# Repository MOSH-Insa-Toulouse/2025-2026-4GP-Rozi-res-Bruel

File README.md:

# 2025-2026-4CP - Projet de capteur low-tech en graphite - Marilou Rozières & Adélaïs Bruel 

## SOMMAIRE
*** 
  - [I. Contexte et description du projet](#contexte-et-description-du)
  - [II. Livrables](#livrables)
  - [III. Matériel nécessaire](#matériel-nécessaire)
  - [IV. Conditionnement analogique](#conditionnement-analogique)
  - [V. Modélisaiotn et simulation](#modélisaiton-et-simulation)
  - [VI. Conception](#conception)
  - [VII. Fabrication](#fabrication)
  - [VIII. Développement firmware et software](#développement-firmware-et-software)
  - [IX. Analyse et caractérisation](#analyse-et-caractérisation)
  - [X. Datasheet](#datasheet)
  - [XI. Conclusion](#conclusion)

*** 

## Contexte et description du projet 

&nbsp;&nbsp;&nbsp;&nbsp;&nbsp;&nbsp;Ce projet s'inscrit dans le cadre de l'UF "Du capteur au banc de test" de la 4ème année Génie Physique de l'INSA Toulouse. 
L'objectif de ce projet est de concevoir, modéliser, prototyper, caractériser et analyser un capteur de déformation low-tech.

&nbsp;&nbsp;&nbsp;&nbsp;&nbsp;&nbsp;Le principe de fonctionnement du capteur repose sur la piézorésistivité d'un dépôt de graphite (réalisé à l'aide d'un simple crayon de bois) sur un support flexible (une feuille de papier). 
Microscopiquement, le trait de crayon est un agglomérat de feuillets de graphite. Dans ce milieu granulaire complexe, la conduction se fait principalement par effet tunnel : les nombreux grains sont séparés par de très fins interstices, la probabilité de passage des électrons d'un grain de graphite à l'autre par franchissement de l'interstice est non nulle si cette barrière est suffisament fine. Cette probabilité dépend exponentiellement de la distance *d* qui sépare les deux grains.
Ce paramètre physique est alors à l'origine de la variation de résistance : en tension, l'écart *d* entre les particules augmente, la probabilité de passage est plus faible, la résistance globale du capteur augmente. 
Tandis qu'en compression, la distance *d* diminue, les particules se rapprochent, la probabilité d'échange augmente, la résistance chute. 
La dépendance exponentielle de la résistance à la distance *d* explique pourquoi une très faible variation du capteur va nous permettre de lire des varirations de signal (résistance) importantes. 

&nbsp;&nbsp;&nbsp;&nbsp;&nbsp;Pour passer d'un trait de crayon à un capteur fonctionnel, le projet s'est déroulé selon ces différentes phases :
- **Conditionnement analogique** : Conception d'un amplificateur transimpédance (conversion courant-tension) pour transformer les variations de courant (de l'ordre du nA) en un signal de tension exploitable (0−5V).
- **Modélisation et Simulation** : Utilisation de LTSpice pour dimensionner les filtres actifs et passifs afin d'éliminer le bruit parasite (notamment le 50 Hz du secteur).
- **Conception** : Routage d'un circuit imprimé (Shield PCB) sous KiCad pour intégrer l'électronique, l'écran OLED et le module Bluetooth.
- **Fabrication** : Réalisation physique du PCB par insolation, gravure chimique (perchlorure de fer), perçage et soudure des composants.
- **Développement Firmware & Software** : Programmation de la carte Arduino (gestion de l'I2C, SPI et UART) et création d'une interface mobile sous MIT App Inventor.
- **Analyse** : Caractérisation du capteur sur un banc de test dédié et rédaction d'une datasheet technique.

Ce document a pour objectif d'expliciter ces différentes étapes.  

## Livrables 
Les livrables attendus sont les suivants : 
- **Un shield PCB connecté à une carte arduino UNO** avec différents composants : un capteur graphite, un amplificateur transimpédance, un module bluetooth, un écran OLED, un flex sensor commercial, un potentiomètre digital, un encodeur rotatoire. D'autres composants peuvent être implémentés ;
- **Un code arduino** qui gère les différents composants cités précédemments (mesures de contraintes, échanges bluetooth et OLED, potentiomètre digital et boutons) ;
- **Une application Android** (sous MIT App Inventor) interfaçant le PCB et le code Arduino correspondant;
- **Une datasheet du capteur** reprenant toutes ses caractéristiques ainsi que ses tests.

## Matériel nécessaire

Afin de réaliser notre dispositif électronique, nous avons eu besoin de :

**Pour le montage amplificateur transimpédance :**

- Résistances : une de 1 kΩ, une de 10 kΩ et deux de 100 kΩ - une troisième de 100 kΩ peut être prévue, mais peut aussi être substituée par une résistance variable (le potentiomètre digital), choix que l'on a fait ;
- Potentiomètre digital MCP41050 et son support ;
- Amplificateur opérationnel LTC1050 et son support ;
- Capacités : trois de 100 nF et une de 1 μF.

**Pour le reste du dispositif :**

- Arduino Uno et son câble d’alimentation ;
- Résistance : une de 47kΩ pour le flex sensor ;
- Module Bluetooth HC05 ;
- Ecran OLED de dimension 128*64 ;
- Flex sensor ;
- Encodeur rotatoire ;
- Capteur graphite et 2 pinces crocodiles ;
- 20 sockets ;
- 35 headers.

## Conditionnement analogique 

&nbsp;&nbsp;&nbsp;&nbsp;&nbsp;Le capteur en graphite présente une résistance extrêmement élevée (de l'ordre du MΩ), ce qui génère des courants infimes (pico- à nanoampères) sous une tension de 5 V. Pour transformer ce signal en une tension exploitable par l’ADC d'une Arduino UNO (0−5V), nous avons conçu un amplificateur transimpédance, réalisé comme suit : 

Nous avons utilisé l’AOP LTC1050 car il possède un courant de biais d'entrée extrêmement faible et un offset quasi nul, évitant ainsi de fausser les mesures de courants très faibles. 
Nous avons placé une résistance de protection (R5) en entrée pour protéger l'AOP contre les décharges électrostatiques, ainsi qu'une résistance du shunt (R1) qui assure la référence à la masse. La résistance de rétroaction (R2) a été subsitué par un potentiomètre digital MCP41050 pour ajuster dynamiquement le gain du montage via le code Arduino. 
Les trois étages de filtrages de cet amplificateur permet de minimiser au maximum les bruits parasites. 

## Modélisation et simulation 

&nbsp;&nbsp;&nbsp;&nbsp;&nbsp;Avant la fabrication, l'ensemble du circuit a été modélisé sous LTSpice pour vérifier que l'amplification convertit bien les nanoampères en une tension comprise entre 0 et 5V. Cette modélisation a également permis de valider l'efficacité de nos trois étage de filtrage :  
- Filtre passe-bas (16 Hz) : élimination des hautes fréquences parasites.
- Filtre passe-bas (1,6 Hz) : atténuation drastique du bruit secteur (50 Hz)
- Filtre passe-bas (1,6 kHz) : supression des interférences liées à la communication de l'ADC.

## Conception 
&nbsp;&nbsp;&nbsp;&nbsp;&nbsp;La phase de conception a été réalisée sur Kicad. L'ojectif était de créer un Shield compatible avec le format de l'Arduino UNO. 
Cela nous demandé trois étapes : 
- Saisie des empreintes et des shématics associés pour nos différents composants : AOP, potentiomètre digital, écran OLED, encodeur rotatoire et module bluetooth. 
- Le routage du PCB : optimisation du placement des composants pour réduire les longueurs de pistes et visualisation 3D des composants pour vérifier l'abscence de conflits mécaniques entre tous les composants.
- Ajout d'un plan de masse pour minimiser le bruit électromagnétique et stabiliser les mesures de hautes impédances.

## Fabrication 
&nbsp;&nbsp;&nbsp;&nbsp;&nbsp;La réalisation du prototype a été faite par ce processus de fabrication : 
- Insolation & gravure (réalisé par Catherine Crouzet) : transfert du masque de gravure sur une plaque époxy et passage au perchlorure de fer.
- Nettoyage (réalisé par Catherine Crouzet) : Retrait de la résine photosensible à l'acétone pour révéler les pistes de cuivre.
- Percage & soudure : montage manuel des composants sur le PCB final.
- Assemblage : soudure des composants.

## Développement Firmaware et Software 

Le système est piloté par deux pôles : 
- Firmware (Arduino) : utilisation des bibliothèques *Adafruit_SSD1306* (OLED), *SPI* (potentiomètre) et *SoftwareSerial* (Bluetooth). Le code génère un menu intéractif via l'encodeur rotatoire pour calibrer le capteur et lancer les mesures.
- Interface mobile : développement d'une application Android sur MIT App Inventor qui communique en Bluetooth pour afficher la résistance en temps réel et tracer la courbe de déformation directement sur le smartphone.

## Analyse et caractérisation

**Dispositif de mesure :** 

&nbsp;&nbsp;&nbsp;&nbsp;&nbsp;Afin d’obtenir les caractéristiques spécifiques du capteur, nous avons utilisé un banc de test composé de six cylindres de diamètre différent, permettant d’étudier la résistance de notre capteur en tension et en compression pour six valeurs de contraintes connues.  

&nbsp;&nbsp;&nbsp;&nbsp;&nbsp;Nous avons choisi d’étudier trois types de crayons à papier différent : le B, le 3B et le 6B. Nous avons donc conçu trois capteurs différents, et avons déterminé pour chacun d’entre eux douze valeurs : six en compression et six en tension. Ces mesures nous ont permises d’établir la variation relative de résistance en fonction de la déformation grâce aux formules suivantes : 

Calcul de la déformation ∶ ε=  e/D

Avec e l’épaisseur du papier utilisé pour le capteur et D le diamètre du cylindre sur lequel est effectué la mesure. 

Calcul de la variation relative de résistance∶ ∆R/R0 (%)=  (R_mesuré-R0)/R0

**Résultats des mesures :**

En tension, nous obtenons alors la variation relative de résistance en fonction de la déformation suivante : 

En compression, nous obtenons la variation relative de la résistance en fonction de la déformation suivante : 

&nbsp;&nbsp;&nbsp;&nbsp;&nbsp;Les allures des courbes sont pertinentes : les crayons à papier sont constitués de graphite et d’un liant isolant (argile). Afin de comprendre la différence entre les différents types de crayons (B, 3B, 6B, …) il faut se pencher sur le seuil de percolation de ceux-ci. Le seuil de percolation représente la fraction volumique nécessaire de charge conductrice (ici le graphite) afin que celles-ci forment un réseau continu interconnecté à travers la matrice isolante (l’argile). A partir de ce seuil de matière conductrice, les propriétés macroscopiques du matériau basculent d’un comportement isolant à un comportement conducteur. Un crayon 6B est saturé en graphite et contient très peu d’argile (seuil de percolation largement dépassé), il représente alors un milieu très conducteur. Quand une déformation est appliquée au capteur, des micro fissures sont créées, mais il existe une multitude de chemins secondaires conducteurs, la résistance globale du capteur n’est que très peu impactée. A contrario, le crayon B a une mine dure, il contient une forte proportion d’argile (très proche du seuil de percolation), les grains de graphite sont plus dispersés dans la matrice d’argile isolante, lorsqu’une déformation est appliquée, les rares chemins électriques entre les grains de graphite se brise très facilement, la résistance varie alors fortement. 

**Analyse :**

&nbsp;&nbsp;&nbsp;&nbsp;&nbsp;La sensibilité (facteur de jauge k) est définie par : k=  (∆R/R0)/ε
Le crayon B possède la meilleure sensibilité puisque pour une déformation donnée il génère une plus grande variation de résistance. Diminuer la concentration de charge conductrice (en passant de 6B à B) augmente alors fortement la piézorésistivité du matériau. 
Pour conclure, pour une application requérant une grande sensibilité un capteur réalisé avec un crayon de type B est le mieux, néanmoins celui-ci aura tendance à « s’user » plus vite puisque que sa composition est au niveau du seuil de percolation. Tandis que pour une application nécessitant moins de précision mais plus de robustesse, un crayon très gras tel que le 6B conviendra mieux, puisque qu’étant très loin du seuil de percolation il peut être déformé plus de fois avant de ne plus avoir chemins conducteurs possible entre les particules.  

## Datasheet
La datasheet du capteur est disponible [ici](https://github.com/MOSH-Insa-Toulouse/2025-2026-4GP-Rozi-res-Bruel/blob/main/DATASHEET/DATASHEET.pdf)

## Conclusion 
&nbsp;&nbsp;&nbsp;&nbsp;&nbsp;Pour conclure ce projet, ce capteur low tech est adapté non pas à la lecture d’une valeur de résistance et donc de déformation mais plutôt à la détection d’un mouvement. Il serait également intéressant dans une application jetable puisque qu’au bout de 5/10 utilisations il n’est plus fonctionnel.

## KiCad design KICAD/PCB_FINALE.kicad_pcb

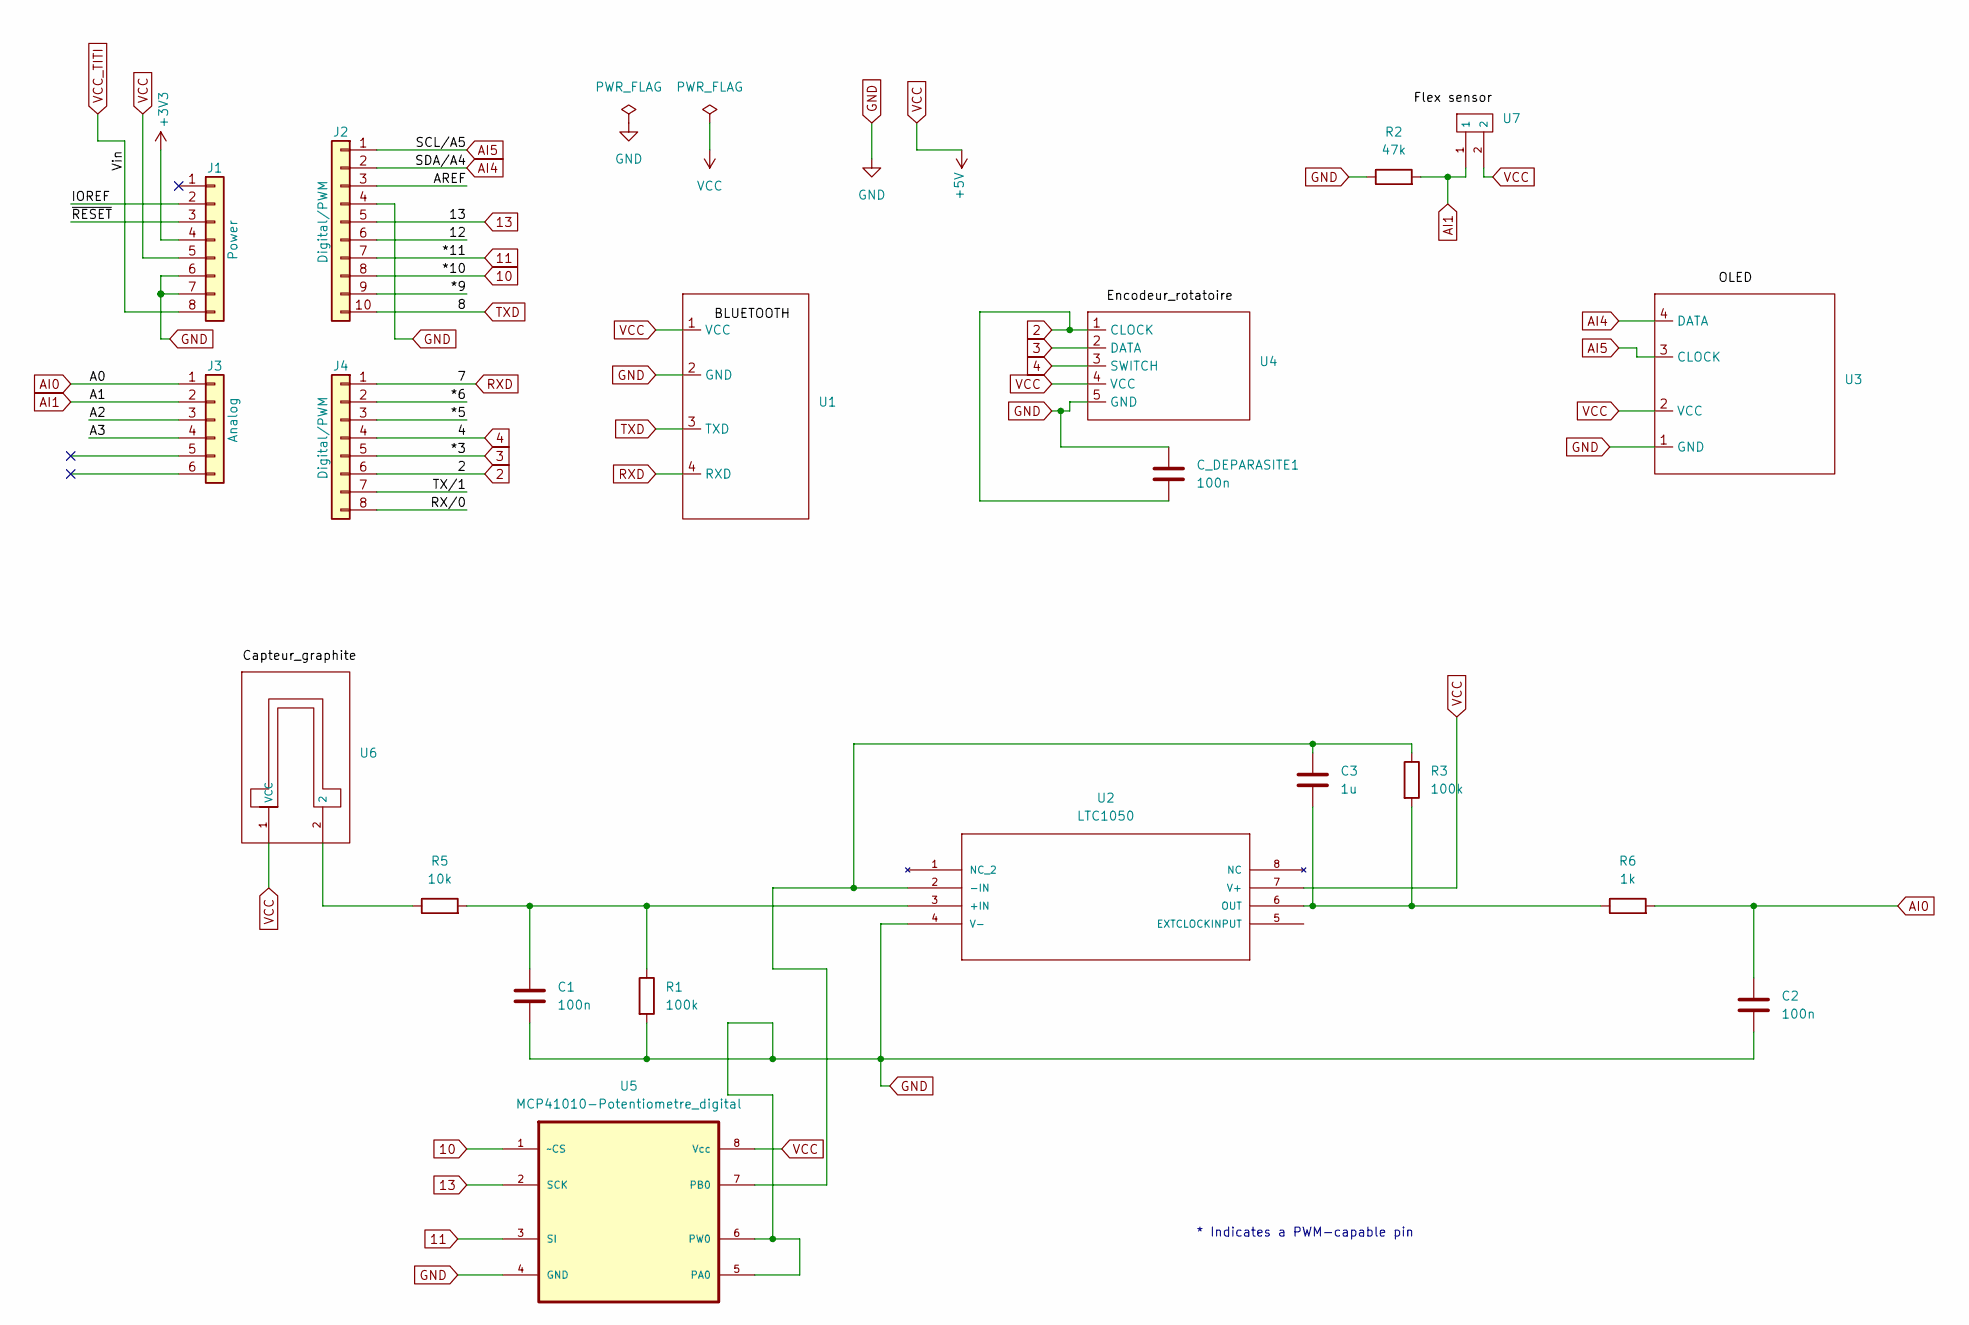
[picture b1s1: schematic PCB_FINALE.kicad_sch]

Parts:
C1, C2: 100n; CapaOk
C3: 1u; CapaOk
C_DEPARASITE1: 100n; CapaOk
J1: Power; PinSocket_1x08_P2.54mm_Vertical
J2: Digital/PWM; PinSocket_1x10_P2.54mm_Vertical
J3: Analog; PinSocket_1x06_P2.54mm_Vertical
J4: Digital/PWM; PinSocket_1x08_P2.54mm_Vertical
R1, R3: 100k; RES5
R2: 47k; RES5
R5: 10k; RES5
R6: 1k; RES5
U1: Bluetouth_HC05
U2: LTC1050; PDIP-8_N; MANUFACTURER_PART_NUMBER ltc1050cn8
U3: OLED_EMPREINTE
U4: ENCODEUR_ROTATOIRE
U5: MCP41010-Potentiometre_digital; Potentiomètre_digital
U6: capteur_graphite
U7: FLEX_SENSOR

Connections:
2: C_DEPARASITE1.2, J4.6, U4.1 (CLOCK)
3: J4.5, U4.2 (DATA)
4: J4.4, U4.3 (SWITCH)
10: J2.8, U5.1 (~CS)
11: J2.7, U5.3 (SI)
13: J2.5, U5.2 (SCK)
+3V3: J1.4
/12: J2.6
/*5: J4.3
/*6: J4.2
/*9: J2.9
/A2: J3.3
/A3: J3.4
/AREF: J2.3
/IOREF: J1.2
/RX/0: J4.8
/TX/1: J4.7
/~RESET: J1.3
AI0: C2.1, J3.1, R6.2
AI1: J3.2, R2.2, U7.1
AI4: J2.2, U3.4 (DATA)
AI5: J2.1, U3.3 (CLOCK)
GND: C1.2, C2.2, C_DEPARASITE1.1, J1.6, J1.7, J2.4, R1.2, R2.1, U1.2 (GND), U2.4 (V-), U3.1 (GND), U4.5 (GND), U5.4 (GND), U5.5 (PA0), U5.6 (PW0)
unnamed: R5.1, U6.2
unnamed: C1.1, R1.1, R5.2, U2.3 (+IN)
unnamed: C3.1, R3.1, U2.2 (-IN), U5.7 (PB0)
unnamed: C3.2, R3.2, R6.1, U2.6 (OUT)
RXD: J4.1, U1.4 (RXD)
TXD: J2.10, U1.3 (TXD)
VCC: J1.5, U1.1 (VCC), U2.7 (V+), U3.2 (VCC), U4.4 (VCC), U5.8 (Vcc), U6.1 (VCC), U7.2
VCC_TITI: J1.8

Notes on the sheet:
* Indicates a PWM-capable pin

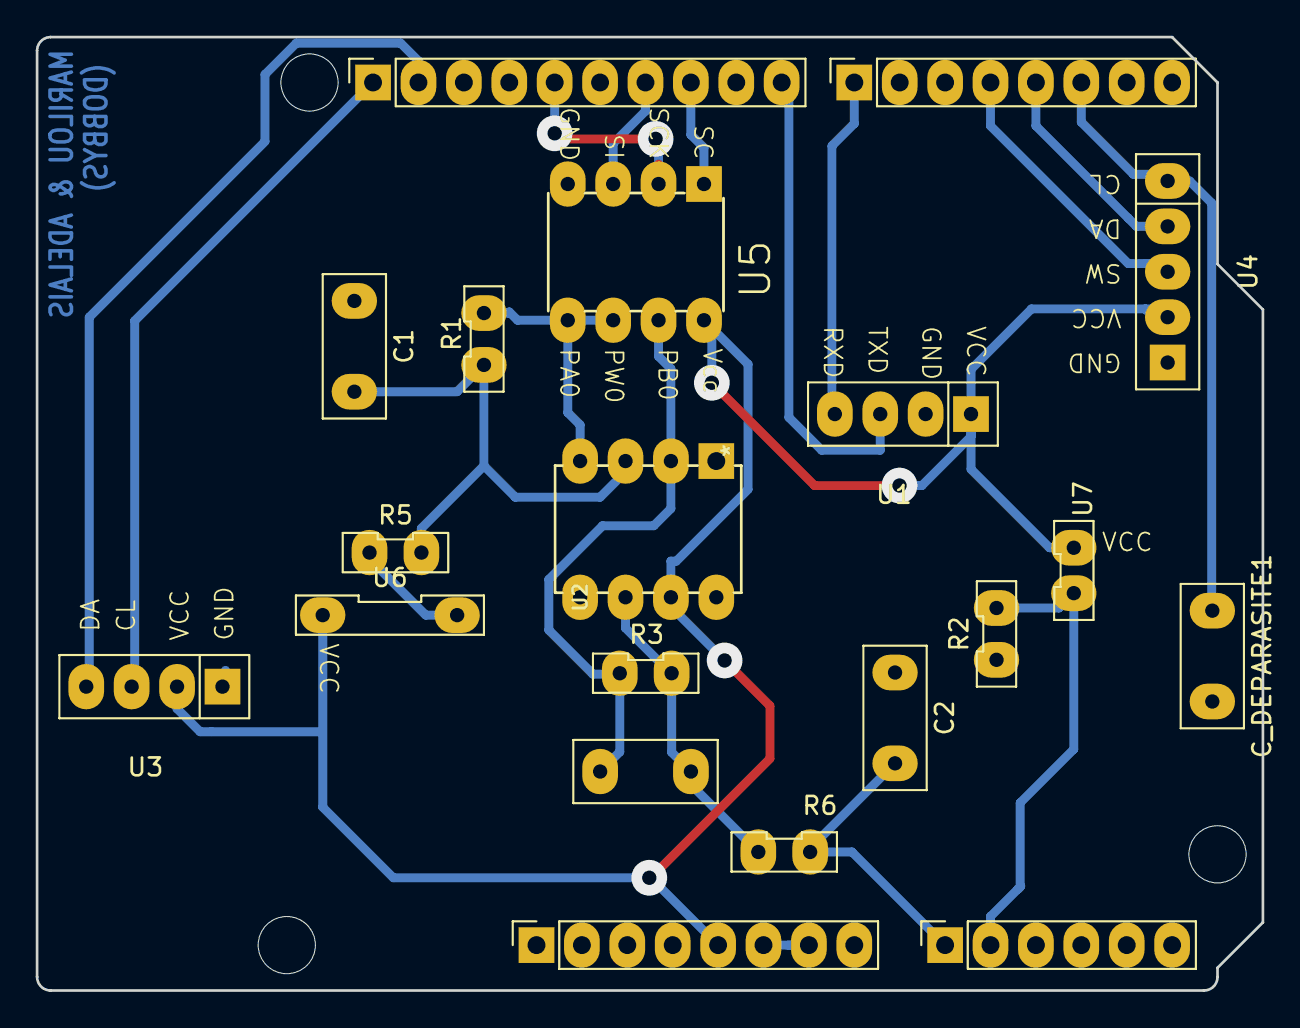
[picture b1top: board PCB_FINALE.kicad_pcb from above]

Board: 2 copper layers, 68.6 x 53.3 mm, 23 parts (0 on the bottom side), 18 nets.

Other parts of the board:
MH1, MH2, MH4: MountingHole_3.2mm

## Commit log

2026-03-12 Create CODE_ARDUINO
2026-03-12 Create DATASHEET
2026-03-17 Add empreinte_library
2026-03-17 vide
2026-03-27 version 1 readme
    Added detailed project documentation including context, deliverables, required materials, and phases of engineering for a low-tech graphite sensor project.
2026-03-27 version2 readme
2026-03-27 Fix header level for 'Matériel nécessaire' section
2026-03-27 Enhance README with additional details and photos
    Added photos and improved descriptions for analog conditioning, modeling, design, and fabrication sections.
2026-03-27 Revise README for analog conditioning and simulation details
    Updated the description of the analog conditioning section, including details about the LTC1050 op-amp and modifications to the feedback resistor. Enhanced the modeling and simulation section to clar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
2026-03-27 ajout photo
    Corrected text for clarity and coherence in the project description, specifically regarding the operation principle of the sensor and its engineering phases.
2026-03-27 photo
    Clarified the description of the amplifier circuit and added details about the filtering stages.
2026-03-27 photos
    Added images and improved formatting in the README.
2026-03-27 photos
    Updated the image in the analog conditioning section and added details about the components used in the amplifier design.
2026-03-27 Fix typo in 'Développement Firmware et Software' section
2026-04-11 ajout italique
    Updated the explanation of the sensor's operation to include variables in italics for clarity.
2026-04-11 Adjust image sizes and alt text in README
    Updated image dimensions and descriptions in the README.
2026-04-11 Revise analysis and characterization in README
    Updated the analysis and characterization section with detailed explanations about the measurement device and results. Clarified the sensitivity factor and its implications for different pencil types.
2026-04-11 Enhance README formatting and analysis content
    Updated formatting and added details in the analysis section of the README.
2026-04-11 Add compression results section to README
2026-04-13 Update README to remove servo motor references
    Removed mention of the servo motor from the analysis and deliverables sections in the README.
2026-04-13 Revise analysis and conclusion in README.md
    Updated the analysis and conclusion sections to clarify the differences between pencil types and their conductivity characteristics.
2026-04-15 Fix spelling error in README.md
    Corrected the spelling of 'trois' in the description of pencil types.
2026-04-15 Create test
2026-04-16 Revise README with system overview and analysis section
    Updated the README to include details about the mobile interface and measurement device.
2026-04-16 ajout photos
2026-04-16 redimensionnement photo
    Updated images in the README to new sources.
2026-06-01 Add conclusion about sensor's functionality and use cases
    Added a conclusion section discussing the sensor's application and limitations.

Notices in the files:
parts and their libraries:
COPYRIGHT: Copyright C 2016 Accelerated Designs. All rights reserved
